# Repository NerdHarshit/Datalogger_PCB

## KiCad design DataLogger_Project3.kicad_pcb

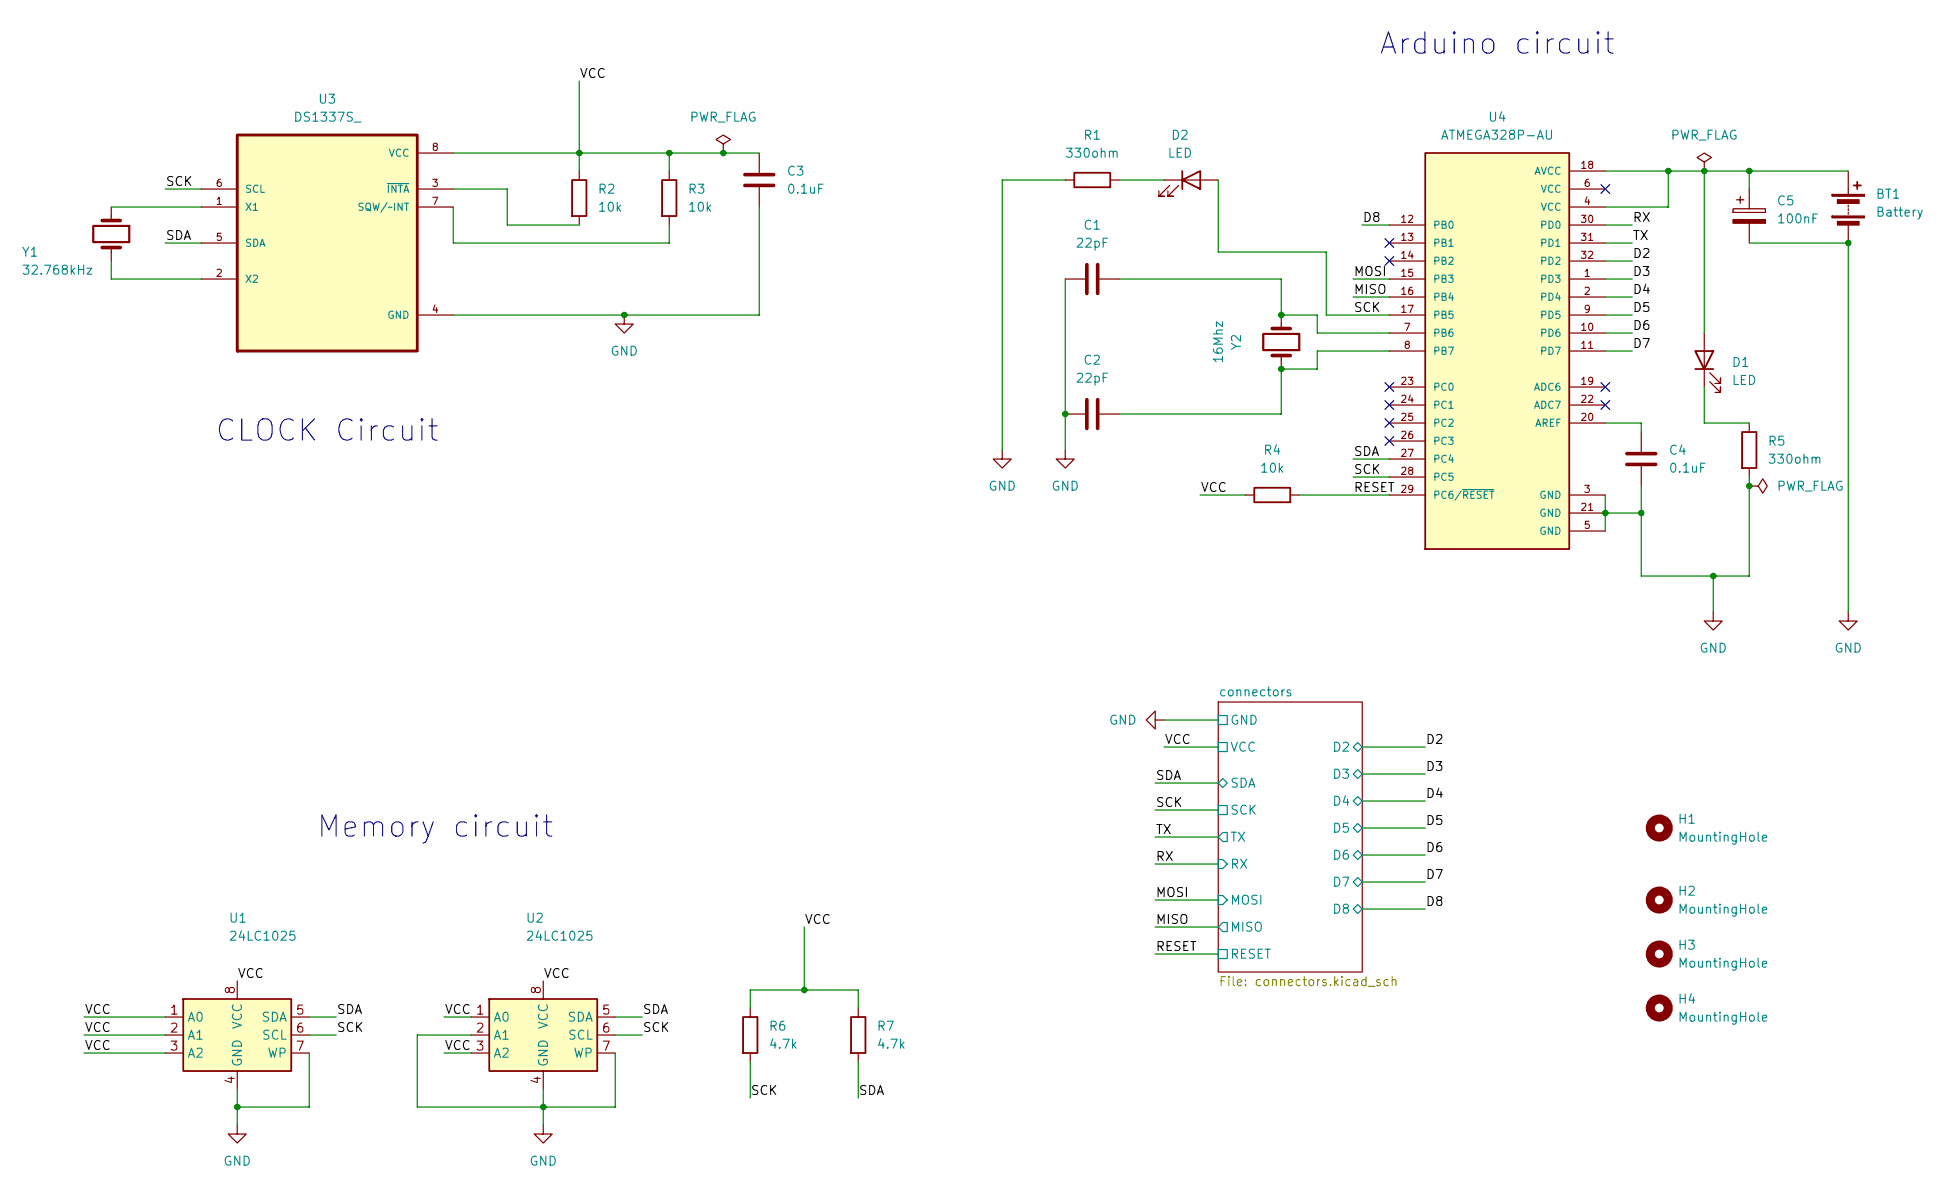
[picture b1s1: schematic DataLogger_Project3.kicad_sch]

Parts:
BT1: Battery; PinHeader_1x02_P2.54mm_Vertical
C1, C2: 22pF; C_0805_2012Metric
C3, C4: 0.1uF; C_0805_2012Metric
C5: 100nF; C_0805_2012Metric
D1, D2: LED; LED_0805_2012Metric
H1, H2, H3, H4: MountingHole; MountingHole_2.1mm
R1, R5: 330ohm; R_0805_2012Metric
R2, R3, R4: 10k; R_0805_2012Metric
R6, R7: 4.7k; R_0805_2012Metric
U1, U2: 24LC1025; SOIC-8_5.3x5.3mm_P1.27mm
U3: DS1337S_; SOIC127P600X175-8N
U4: ATMEGA328P-AU; QFP80P900X900X120-32N; PARTREV 8271A
Y1: 32.768kHz; Crystal_SMD_5032-2Pin_5.0x3.2mm_HandSoldering
Y2: 16Mhz; Crystal_SMD_5032-2Pin_5.0x3.2mm_HandSoldering

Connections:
/D2: U4.32 (PD2); also elsewhere on the board
/D3: U4.1 (PD3); also elsewhere on the board
/D4: U4.2 (PD4); also elsewhere on the board
/D5: U4.9 (PD5); also elsewhere on the board
/D6: U4.10 (PD6); also elsewhere on the board
/D7: U4.11 (PD7); also elsewhere on the board
/D8: U4.12 (PB0); also elsewhere on the board
/MISO: U4.16 (PB4); also elsewhere on the board
/MOSI: U4.15 (PB3); also elsewhere on the board
/RESET: R4.2, U4.29 (PC6/~RESET); also elsewhere on the board
/RX: U4.30 (PD0); also elsewhere on the board
/SCK: D2.2 (A), R6.2, U1.6 (SCL), U2.6 (SCL), U3.6 (SCL), U4.17 (PB5), U4.28 (PC5); also elsewhere on the board
/SDA: R7.2, U1.5 (SDA), U2.5 (SDA), U3.5 (SDA), U4.27 (PC4); also elsewhere on the board
/TX: U4.31 (PD1); also elsewhere on the board
/VCC: C3.1, R2.1, R3.1, R4.1, R6.1, R7.1, U1.1 (A0), U1.2 (A1), U1.3 (A2), U1.8 (VCC), U2.1 (A0), U2.3 (A2), U2.8 (VCC), U3.8 (VCC); also elsewhere on the board
GND: BT1.2 (-), C1.1, C2.1, C3.2, C4.1, C5.2, R1.1, R5.2, U1.4 (GND), U1.7 (WP), U2.2 (A1), U2.4 (GND), U2.7 (WP), U3.4 (GND), U4.3 (GND), U4.5 (GND), U4.21 (GND); also elsewhere on the board
unnamed: BT1.1 (+), C5.1, D1.2 (A), U4.4 (VCC), U4.18 (AVCC)
unnamed: D1.1 (K), R5.1
unnamed: D2.1 (K), R1.2
unnamed: R3.2, U3.7 (SQW/~INT)
unnamed: U3.1 (X1), Y1.1
unnamed: U3.2 (X2), Y1.2
unnamed: R2.2, U3.3 (~INTA)
unnamed: C4.2, U4.20 (AREF)
unnamed: C1.2, U4.7 (PB6), Y2.2
unnamed: C2.2, U4.8 (PB7), Y2.1

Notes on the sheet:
Memory circuit
CLOCK Circuit
Arduino circuit

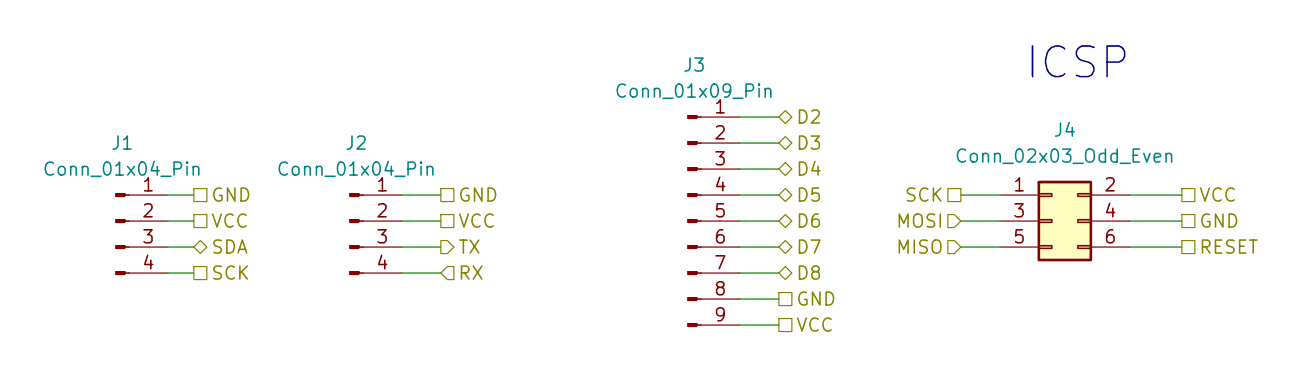
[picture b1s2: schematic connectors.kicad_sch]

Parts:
J1, J2: Conn_01x04_Pin; PinHeader_1x04_P2.54mm_Vertical
J3: Conn_01x09_Pin; PinHeader_1x09_P2.54mm_Vertical
J4: Conn_02x03_Odd_Even; PinHeader_2x03_P2.54mm_Vertical

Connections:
/D2: J3.1; also elsewhere on the board
/D3: J3.2; also elsewhere on the board
/D4: J3.3; also elsewhere on the board
/D5: J3.4; also elsewhere on the board
/D6: J3.5; also elsewhere on the board
/D7: J3.6; also elsewhere on the board
/D8: J3.7; also elsewhere on the board
/MISO: J4.5; also elsewhere on the board
/MOSI: J4.3; also elsewhere on the board
/RESET: J4.6; also elsewhere on the board
/RX: J2.4; also elsewhere on the board
/SCK: J1.4, J4.1; also elsewhere on the board
/SDA: J1.3; also elsewhere on the board
/TX: J2.3; also elsewhere on the board
/VCC: J1.2, J2.2, J3.9, J4.2; also elsewhere on the board
GND: J1.1, J2.1, J3.8, J4.4; also elsewhere on the board

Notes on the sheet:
ICSP

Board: 2 copper layers, 29 parts (0 on the bottom side), 26 nets, no tracks yet.

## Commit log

2025-10-30 created project
2025-10-30 added symbols and footprints
2025-10-30 added values
2025-11-05 added footprints
2025-11-05 wired the components
2025-11-05 finalising the schema
2025-11-05 made layout of 2 layer
2025-11-05 added layout
2025-11-08 changed layout
2025-11-08 finished routing 2 layer pcb
